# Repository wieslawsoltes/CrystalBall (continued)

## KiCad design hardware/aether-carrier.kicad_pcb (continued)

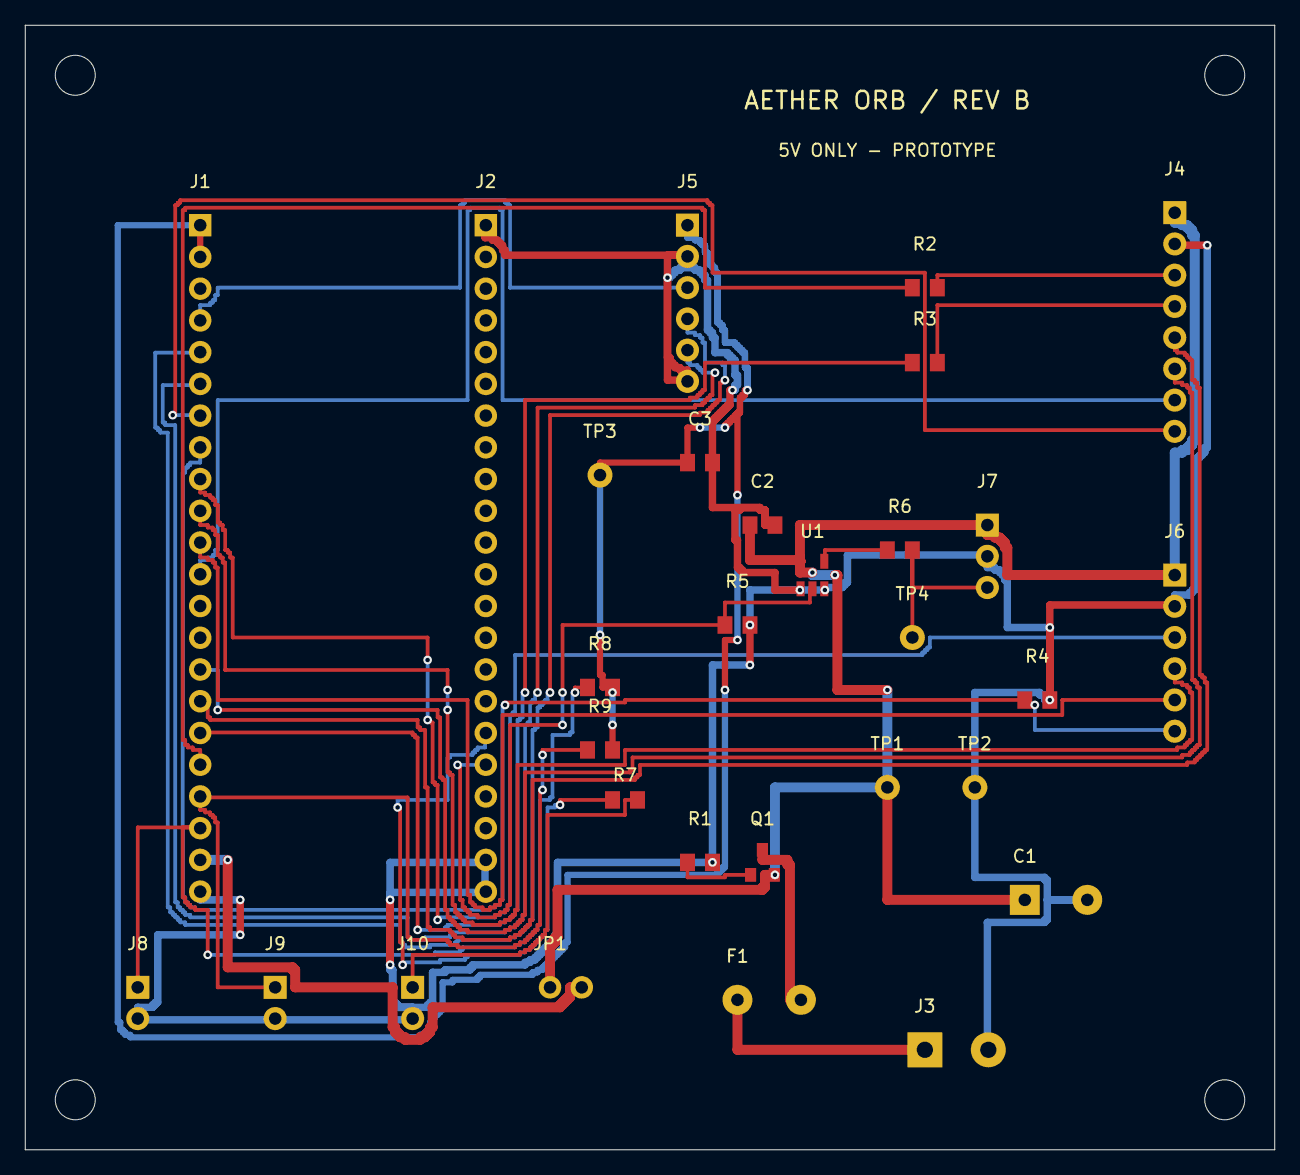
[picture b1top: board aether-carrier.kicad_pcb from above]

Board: 2 copper layers, 100.0 x 90.0 mm, 34 parts (0 on the bottom side), 29 nets.

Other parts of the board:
H1, H2, H3, H4: MountingHole_3.2

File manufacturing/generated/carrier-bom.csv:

Reference,Qty,Value,Candidate ordering code,Fitted,Footprint,Qualification,Notes,Source
J1,1,DevKitC-1 socket J1,Samtec SSQ-122-03-G-S,True,Aether:Socket_1x22_P2.54_J1,CANDIDATE; supplier drawing/FAI required,Use genuine ESP32-S3-DevKitC-1-N8R8 v1.1. Remove module before USB flashing.,https://docs.espressif.com/projects/esp-dev-kits/en/latest/e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
J2,1,DevKitC-1 socket J3,Samtec SSQ-122-03-G-S,True,Aether:Socket_1x22_P2.54_J2,CANDIDATE; supplier drawing/FAI required,Use genuine ESP32-S3-DevKitC-1-N8R8 v1.1. Remove module before USB flashing.,https://docs.espressif.com/projects/esp-dev-kits/en/latest/e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
J3,1,5V INPUT,Phoenix Contact 1729128,True,Aether:Terminal_1x02_P5.08_J3,CANDIDATE; supplier drawing/FAI required,5.08 mm 2-position terminal; 5 V only. + pin 1; - pin 2. Verify exact holder body.,https://www.phoenixcontact.com/en-us/products/pcb-terminal-b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
F1,1,PTC 2.5A,Littelfuse RXEF250,True,Aether:PTC_P5.08_F1,CANDIDATE; supplier drawing/FAI required,"Thermal resettable fuse, not a precise electronic current limiter. Check hold-current derating.",https://www.littelfuse.com/products/polyswitch-resettable-pt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
Q1,1,AO3401A,AO3401A,True,Aether:SOT-23_Q1,CANDIDATE; supplier drawing/FAI required,"P-channel reverse-input protection. Pin 1 G, pin 2 S, pin 3 D. NOT reverse-current blocking while on.",https://www.aosmd.com/res/data_sheets/AO3401A.pdf
R1,1,100k,RC0805FR-07100KL,True,Aether:R_0805_2012Metric_R1,CANDIDATE; supplier drawing/FAI required,,
C1,1,1000uF 10V,Panasonic EEU-FR1A102,True,Aether:CP_Radial_D10_P5_C1,CANDIDATE; supplier drawing/FAI required,Polarized; + pin 1. Measure PD startup/inrush with this bulk capacitance.,https://industrial.panasonic.com/ww/products/pt/aluminum-cap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
JP1,1,RUN POWER,Samtec TSW-102-07-G-S + 2.54mm shunt,True,Aether:PinHeader_1x02_P2.54_JP1,CANDIDATE; supplier drawing/FAI required,Fitted shunt for RUN. Remove DevKit completely for USB flashing; do not dual-power.,
J4,1,LCD,JST B8B-XH-A(LF)(SN),True,Aether:XH_1x08_P2.50_J4,CANDIDATE; supplier drawing/FAI required,Vertical keyed XH header; pin 1 is square; qualify exact supplier drawing.,https://www.jst-mfg.com/product/pdf/eng/eXH.pdf
R2,1,33R,RC0805FR-0733RL,True,Aether:R_0805_2012Metric_R2,CANDIDATE; supplier drawing/FAI required,,
R3,1,33R,RC0805FR-0733RL,True,Aether:R_0805_2012Metric_R3,CANDIDATE; supplier drawing/FAI required,,
J5,1,MIC 3V3,JST B6B-XH-A(LF)(SN),True,Aether:XH_1x06_P2.50_J5,CANDIDATE; supplier drawing/FAI required,Vertical keyed XH header; pin 1 is square; qualify exact supplier drawing.,https://www.jst-mfg.com/product/pdf/eng/eXH.pdf
J6,1,AMP 5V,JST B6B-XH-A(LF)(SN),True,Aether:XH_1x06_P2.50_J6,CANDIDATE; supplier drawing/FAI required,Vertical keyed XH header; pin 1 is square; qualify exact supplier drawing.,https://www.jst-mfg.com/product/pdf/eng/eXH.pdf
R4,1,10k,RC0805FR-0710KL,True,Aether:R_0805_2012Metric_R4,CANDIDATE; supplier drawing/FAI required,,
U1,1,SN74AHCT1G125,SN74AHCT1G125DBVR,True,Aether:SOT-23-5_U1,CANDIDATE; supplier drawing/FAI required,5V TTL input buffer; /OE grounded. Qualify TI DBV footprint before ordering.,https://www.ti.com/lit/ds/symlink/sn74ahct1g125.pdf
C2,1,100nF,GRM21BR71H104KA01L,True,Aether:C_0805_2012Metric_C2,CANDIDATE; supplier drawing/FAI required,,
R5,1,100k,RC0805FR-07100KL,True,Aether:R_0805_2012Metric_R5,CANDIDATE; supplier drawing/FAI required,,
R6,1,330R,RC0805FR-07330RL,True,Aether:R_0805_2012Metric_R6,CANDIDATE; supplier drawing/FAI required,,
J7,1,RING 5V,JST B3B-XH-A(LF)(SN),True,Aether:XH_1x03_P2.50_J7,CANDIDATE; supplier drawing/FAI required,Vertical keyed XH header; pin 1 is square; qualify exact supplier drawing.,https://www.jst-mfg.com/product/pdf/eng/eXH.pdf
J8,1,PTT,JST B2B-XH-A(LF)(SN),True,Aether:XH_1x02_P2.50_J8,CANDIDATE; supplier drawing/FAI required,Vertical keyed XH header; pin 1 is square; qualify exact supplier drawing.,https://www.jst-mfg.com/product/pdf/eng/eXH.pdf
J9,1,PAGE,JST B2B-XH-A(LF)(SN),True,Aether:XH_1x02_P2.50_J9,CANDIDATE; supplier drawing/FAI required,Vertical keyed XH header; pin 1 is square; qualify exact supplier drawing.,https://www.jst-mfg.com/product/pdf/eng/eXH.pdf
J10,1,REC LED,JST B2B-XH-A(LF)(SN),True,Aether:XH_1x02_P2.50_J10,CANDIDATE; supplier drawing/FAI required,Vertical keyed XH header; pin 1 is square; qualify exact supplier drawing.,https://www.jst-mfg.com/product/pdf/eng/eXH.pdf
R7,1,1k,RC0805FR-071KL,True,Aether:R_0805_2012Metric_R7,CANDIDATE; supplier drawing/FAI required,,
R8,1,10k,RC0805FR-0710KL,True,Aether:R_0805_2012Metric_R8,CANDIDATE; supplier drawing/FAI required,,
R9,1,10k,RC0805FR-0710KL,True,Aether:R_0805_2012Metric_R9,CANDIDATE; supplier drawing/FAI required,,
C3,1,100nF,GRM21BR71H104KA01L,True,Aether:C_0805_2012Metric_C3,CANDIDATE; supplier drawing/FAI required,,
TP1,1,5V_SYS,Keystone 5000 test loop,True,Aether:TestPoint_THT_D2_TP1,CANDIDATE; supplier drawing/FAI required,,
TP2,1,GND,Keystone 5000 test loop,True,Aether:TestPoint_THT_D2_TP2,CANDIDATE; supplier drawing/FAI required,,
TP3,1,3V3,Keystone 5000 test loop,True,Aether:TestPoint_THT_D2_TP3,CANDIDATE; supplier drawing/FAI required,,
TP4,1,LED_DIN,Keystone 5000 test loop,True,Aether:TestPoint_THT_D2_TP4,CANDIDATE; supplier drawing/FAI required,,

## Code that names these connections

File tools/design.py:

"""Aether Orb Rev B: single source for the carrier circuit and interfaces.
Units: mm. Board coordinates: x right, y down, viewed from component side.
This file describes OUR carrier, not the internal circuitry of purchased modules.
"""
from dataclasses import dataclass, asdict
from pathlib import Path
import json
ROOT = Path(__file__).resolve().parents[1]
W, H = 100.0, 90.0
PINMAP = {
    'MIC_BCLK':4, 'MIC_WS':5, 'MIC_SD':6,
    'LCD_BL':7, 'LCD_RST':8, 'LCD_DC':9, 'LCD_CS':10,
    'LCD_MOSI':11, 'LCD_SCK':12,
    'NEXT':13, 'PTT':14, 'AMP_SD':15,
    'AMP_BCLK':16, 'AMP_WS':17, 'AMP_DIN':18,
    'LED_DATA':21, 'REC_LED':47,
}
@dataclass
class Pad:
    number: str
    x: float
    y: float
    net: str
    diameter: float = 1.8
    drill: float = 1.0
    sx: float = 0
    sy: float = 0
    shape: str = 'circle'
    kind: str = 'thru_hole'
@dataclass
class Part:
    ref: str
    value: str
    footprint: str
    x: float
    y: float
    pads: list
    body: tuple
    mpn: str
    note: str = ''
    source: str = ''
    fitted: bool = True
    def abs_pads(self):
        return [dict(asdict(p),x=self.x+p.x,y=self.y+p.y,ref=self.ref) for p in self.pads]
PARTS=[]
def part(ref,value,fp,x,y,pads,body,mpn,note='',source='',fitted=True):
    p=Part(ref,value,fp,x,y,pads,body,mpn,note,source,fitted);PARTS.append(p);return p

def header(ref, label, x,y,nets,pitch=2.5, mpn=None):
    n=len(nets)
    return part(ref,label,f'XH_1x{n:02d}_P{pitch:.2f}',x,y,
        [Pad(str(i+1),0,i*pitch,net,1.85,1.0,shape='rect' if i==0 else 'circle') for i,net in enumerate(nets)],
        (-2.4,-2.5,5.0,(n-1)*pitch+5.0),mpn or f'JST B{n}B-XH-A(LF)(SN)',
        'Vertical keyed XH header; pin 1 is square; qualify exact supplier drawing.',
        'https://www.jst-mfg.com/product/pdf/eng/eXH.pdf')

def resistor(ref,x,y,n1,n2,value,mpn):
    return part(ref,value,'R_0805_2012Metric',x,y,
        [Pad('1',-1.0,0,n1,0,0,1.2,1.4,'rect','smd'),Pad('2',1.0,0,n2,0,0,1.2,1.4,'rect','smd')],
        (-1,-.65,2,1.3),mpn)

def cap(ref,x,y,n1,n2,value='100nF',mpn='GRM21BR71H104KA01L'):
    return part(ref,value,'C_0805_2012Metric',x,y,
        [Pad('1',-1,0,n1,0,0,1.2,1.4,'rect','smd'),Pad('2',1,0,n2,0,0,1.2,1.4,'rect','smd')],
        (-1,-.65,2,1.3),mpn)
# Socket geometry from the official Espressif v1.1 mechanical drawing:
# 25.40 mm PCB width, 1.27 mm edge-to-row offset => 22.86 mm row spacing.
left=['3V3','3V3','NC_EN','MIC_BCLK','MIC_WS','MIC_SD','LCD_BL','AMP_SD','AMP_BCLK','AMP_WS','AMP_DIN','NC_GPIO8_DUP']
# GPIO8 is LCD_RST (header position 12); positions 15+ are GPIO9..14.
left[11]='LCD_RST'
left += ['NC_GPIO3','NC_GPIO46','LCD_DC','LCD_CS','LCD_MOSI','LCD_SCK','NEXT','PTT','DEV_5V','GND']
right=['GND','NC_TX43','NC_RX44','NC_GPIO1','NC_GPIO2','NC_GPIO42','NC_GPIO41','NC_GPIO40','NC_GPIO39','NC_GPIO38','NC_GPIO37','NC_GPIO36','NC_GPIO35','NC_GPIO0','NC_GPIO45','NC_GPIO48','REC_LED','LED_DATA','NC_USB20','NC_USB19','GND','GND']
for ref,x,nets in [('J1',14.0,left),('J2',36.86,right)]:
    part(ref,'DevKitC-1 socket '+('J1' if ref=='J1' else 'J3'),'Socket_1x22_P2.54',x,16,
        [Pad(str(i+1),0,2.54*i,n,1.8,1.0,shape='rect' if i==0 else 'circle') for i,n in enumerate(nets)],
        (-1.4,-1.4,2.8,56.14),'Samtec SSQ-122-03-G-S',
        'Use genuine ESP32-S3-DevKitC-1-N8R8 v1.1. Remove module before USB flashing.',
        'https://docs.espressif.com/projects/esp-dev-kits/en/latest/esp32s3/esp32-s3-devkitc-1/user_guide_v1.1.html')
# External PD module supplies only 5 V. Manual master switch is in its output harness.
part('J3','5V INPUT','Terminal_1x02_P5.08',72,82,
     [Pad('1',0,0,'VIN5',2.8,1.3,shape='rect'),Pad('2',5.08,0,'GND',2.8,1.3)],
     (-2.6,-4,10.3,8),'Phoenix Contact 1729128',
     '5.08 mm 2-position terminal; 5 V only. + pin 1; - pin 2. Verify exact holder body.',
     'https://www.phoenixcontact.com/en-us/products/pcb-terminal-block-mkds-15-2-508-1729128')
part('F1','PTC 2.5A','PTC_P5.08',57,78,
     [Pad('1',0,0,'VIN5',2.4,1.0),Pad('2',5.08,0,'FUSED5',2.4,1.0)],
     (-5.6,-2.1,16.2,4.2),'Littelfuse RXEF250',
     'Thermal resettable fuse, not a precise electronic current limiter. Check hold-current derating.',
     'https://www.littelfuse.com/products/polyswitch-resettable-ptcs/radial-leaded/rxef')
# Reverse-input PMOS: D=input, S=protected output, G=ground via R1.
part('Q1','AO3401A','SOT-23',59,67,
     [Pad('1',-.95,1,'Q_GATE',0,0,.9,1.1,'rect','smd'),
      Pad('2',.95,1,'5V_SYS',0,0,.9,1.1,'rect','smd'),
      Pad('3',0,-1,'FUSED5',0,0,.9,1.1,'rect','smd')],
     (-1.5,-.65,3,1.3),'AO3401A',
     'P-channel reverse-input protection. Pin 1 G, pin 2 S, pin 3 D. NOT reverse-current blocking while on.',
     'https://www.aosmd.com/res/data_sheets/AO3401A.pdf')
resistor('R1',54,67,'Q_GATE','GND','100k','RC0805FR-07100KL')
part('C1','1000uF 10V','CP_Radial_D10_P5',80,70,
     [Pad('1',0,0,'5V_SYS',2.4,1.0,shape='rect'),Pad('2',5,0,'GND',2.4,1.0)],
     (-2.5,-5,10,10),'Panasonic EEU-FR1A102',
     'Polarized; + pin 1. Measure PD startup/inrush with this bulk capacitance.',
     'https://industrial.panasonic.com/ww/products/pt/aluminum-cap/models/EEUFR1A102')
part('JP1','RUN POWER','PinHeader_1x02_P2.54',42,77,
     [Pad('1',0,0,'5V_SYS'),Pad('2',2.54,0,'DEV_5V')],
     (-1.4,-1.4,5.34,2.8),'Samtec TSW-102-07-G-S + 2.54mm shunt',
     'Fitted shunt for RUN. Remove DevKit completely for USB flashing; do not dual-power.')
header('J4','LCD',92,15,['5V_SYS','GND','LCD_SCK_R','LCD_MOSI_R','LCD_CS','LCD_DC','LCD_RST','LCD_BL'])
resistor('R2',72,21,'LCD_SCK','LCD_SCK_R','33R','RC0805FR-0733RL')
resistor('R3',72,27,'LCD_MOSI','LCD_MOSI_R','33R','RC0805FR-0733RL')
header('J5','MIC 3V3',53,16,['3V3','GND','MIC_BCLK','MIC_WS','MIC_SD','GND'])
header('J6','AMP 5V',92,44,['5V_SYS','GND','AMP_BCLK','AMP_WS','AMP_DIN','AMP_SD'])
resistor('R4',81,54,'AMP_SD','GND','10k','RC0805FR-0710KL')
# Gate uses TTL-compatible input thresholds at 5V, not an HC part.
part('U1','SN74AHCT1G125','SOT-23-5',63,44,
    [Pad('1',-.95,1.1,'GND',0,0,.65,1.2,'rect','smd'),
     Pad('2',0,1.1,'LED_DATA',0,0,.65,1.2,'rect','smd'),
     Pad('3',.95,1.1,'GND',0,0,.65,1.2,'rect','smd'),
     Pad('4',.95,-1.1,'LED_5V_BUF',0,0,.65,1.2,'rect','smd'),
     Pad('5',-.95,-1.1,'5V_SYS',0,0,.65,1.2,'rect','smd')],
    (-1.5,-.8,3,1.6),'SN74AHCT1G125DBVR',
    '5V TTL input buffer; /OE grounded. Qualify TI DBV footprint before ordering.',
    'https://www.ti.com/lit/ds/symlink/sn74ahct1g125.pdf')
cap('C2',59,40,'5V_SYS','GND')
resistor('R5',57,48,'LED_DATA','GND','100k','RC0805FR-07100KL')
resistor('R6',70,42,'LED_5V_BUF','LED_DIN','330R','RC0805FR-07330RL')
header('J7','RING 5V',77,40,['5V_SYS','GND','LED_DIN'])
header('J8','PTT',9,77,['PTT','GND'])
header('J9','PAGE',20,77,['NEXT','GND'])
header('J10','REC LED',31,77,['REC_ANODE','GND'])
resistor('R7',48,62,'REC_LED','REC_ANODE','1k','RC0805FR-071KL')
resistor('R8',46,53,'PTT','3V3','10k','RC0805FR-0710KL')
resistor('R9',46,58,'NEXT','3V3','10k','RC0805FR-0710KL')
cap('C3',54,35,'3V3','GND')
# Accessible through-hole test points; no metal enclosure connections.
for i,(x,y,n) in enumerate([(69,61,'5V_SYS'),(76,61,'GND'),(46,36,'3V3'),(71,49,'LED_DIN')],1):
    part(f'TP{i}',n,'TestPoint_THT_D2',x,y,[Pad('1',0,0,n,2.0,1.0)],(-1,-1,2,2),'Keystone 5000 test loop')
HOLES=[(4,4),(96,4),(4,86),(96,86)]
RF_KEEPOUT=(7,0,44,13.5)

def export():
    data={'project':'Aether Orb','revision':'B','board_mm':[W,H],'pinmap':PINMAP,
          'parts':[asdict(p) for p in PARTS], 'holes':HOLES, 'rf_keepout':RF_KEEPOUT,
          'release':'ENGINEERING PROTOTYPE - NOT PRODUCTION RELEASED'}
    (ROOT/'hardware/design.json').write_text(json.dumps(data,indent=2))
    (ROOT/'firmware/main/pins.h').write_text('#pragma once\n// Generated by tools/design.py; do not hand-edit.\n'+
        ''.join(f'#define PIN_{k} {v}\n' for k,v in PINMAP.items()))
    return data
if __name__=='__main__': export()
